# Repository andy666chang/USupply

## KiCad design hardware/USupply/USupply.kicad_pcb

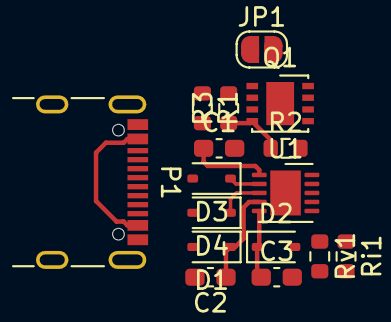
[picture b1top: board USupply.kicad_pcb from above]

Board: 2 copper layers, 16 parts (0 on the bottom side), 12 nets.

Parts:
C1: 1uF; C_0603_1608Metric_Pad1.08x0.95mm_HandSolder
C2, C3: 330pF 50V; C_0603_1608Metric_Pad1.08x0.95mm_HandSolder
D1, D2, D3, D4: TVS; D_SOD-323
JP1: Jumper_2_Open; SolderJumper-2_P1.3mm_Open_RoundedPad1.0x1.5mm
P1: USB_C_Receptacle_USB2.0; USB_C_Receptacle_GCT_USB4105-xx-A_16P_TopMnt_Horizontal
Q1: AGM30P08AP; DFN-8-1EP_3x3mm_P0.65mm_EP1.55x2.4mm
R1: 10 5%; R_0603_1608Metric
R2: 30K 5%; R_0603_1608Metric
R3: 100K 5%; R_0603_1608Metric
Ri1: NC 1%; R_0603_1608Metric
Rv1: NC 1%; R_0603_1608Metric
U1: HUSB238; DFN-10-1EP_3x3mm_P0.5mm_EP1.7x2.5mm

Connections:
/CC1: C2.1, D1.1 (A1), P1.A5 (CC1), U1.4 (CC1)
/CC2: C3.1, D2.1 (A1), P1.B5 (CC2), U1.5 (CC2)
/D+: D3.1 (A1), P1.A6 (D+), P1.B6 (D+), U1.2 (D+)
/D-: D4.1 (A1), P1.A7 (D-), P1.B7 (D-), U1.3 (D-)
/USB_PD/Gate: R2.2, U1.10 (GATE)
GND: C1.2, C2.2, C3.2, D1.2 (A2), D2.2 (A2), D3.2 (A2), D4.2 (A2), P1.A1 (GND), P1.A12 (GND), P1.B1 (GND), P1.B12 (GND), P1.S1 (SHIELD), Ri1.2, Rv1.2, U1.11 (GND)
unnamed: Q1.4 (G), R2.1, R3.1
unnamed: Ri1.1, U1.9 (ISET)
unnamed: C1.1, R1.2, U1.1 (VIN)
unnamed: Rv1.1, U1.8 (VSET)
VBUS: JP1.1 (A), P1.A4 (VBUS), P1.A9 (VBUS), P1.B4 (VBUS), P1.B9 (VBUS), Q1.1 (S), Q1.2 (S), Q1.3 (S), R1.1, R3.2
VDC: JP1.2 (B), Q1.5 (D), Q1.6 (D), Q1.7 (D), Q1.8 (D), Q1.9 (D)
